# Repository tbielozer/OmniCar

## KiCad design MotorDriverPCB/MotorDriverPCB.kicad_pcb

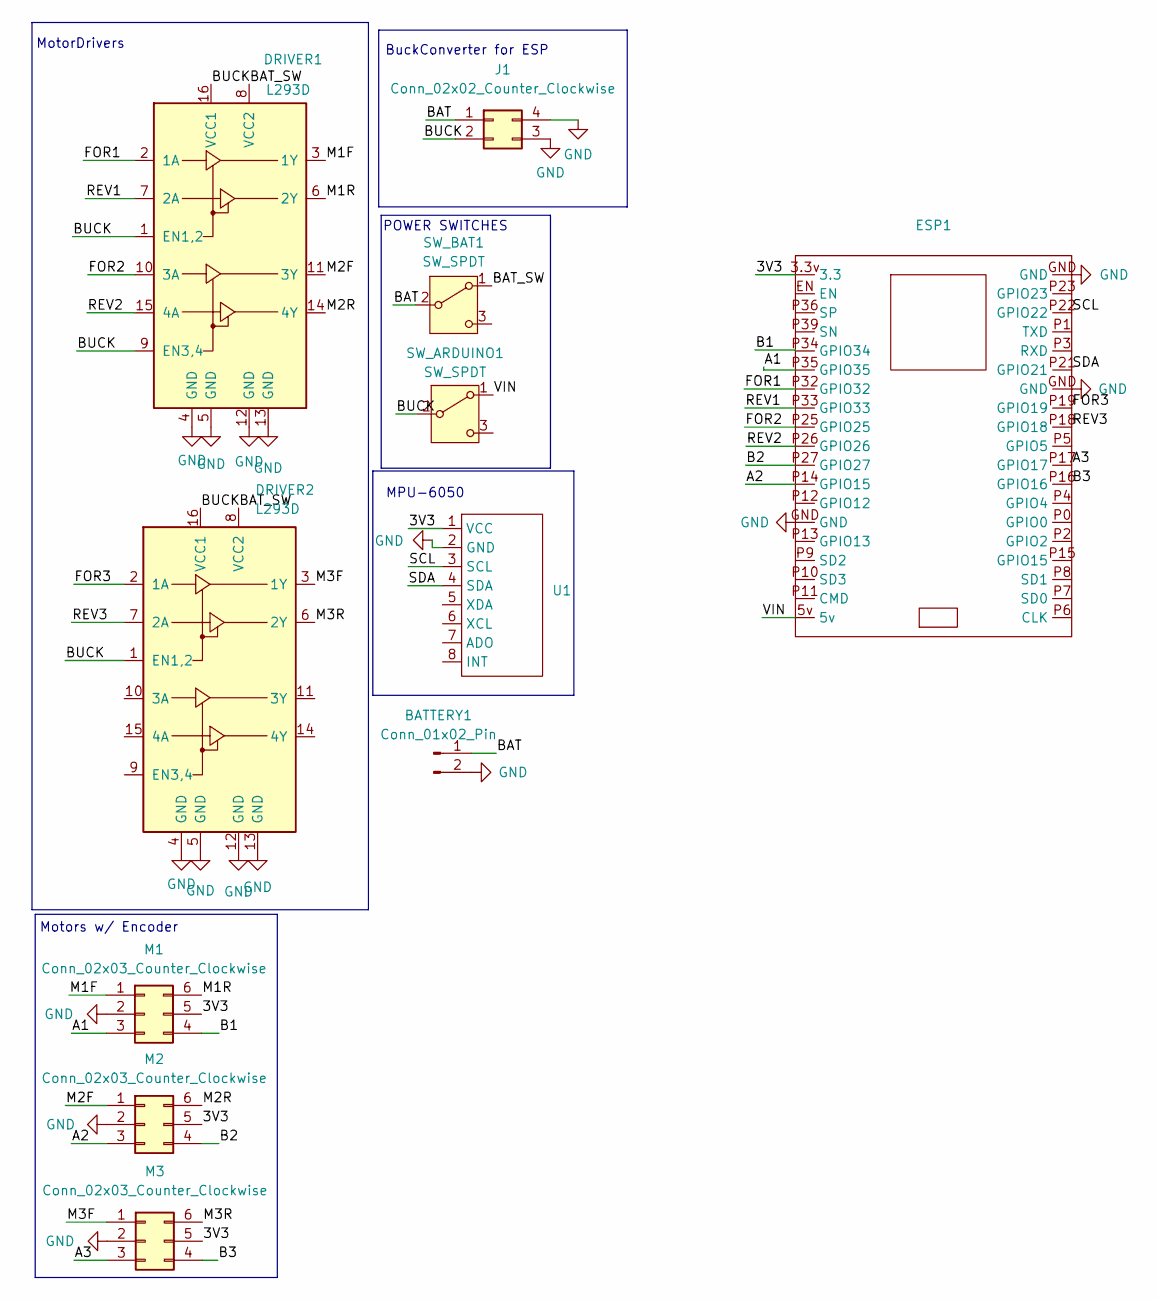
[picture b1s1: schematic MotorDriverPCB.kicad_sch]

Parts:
BATTERY1: Conn_01x02_Pin; PinHeader_1x02_P2.54mm_Vertical
DRIVER1, DRIVER2: L293D; DIP-16_W7.62mm
ESP1: ESP 38pin
J1: Conn_02x02_Counter_Clockwise; PinHeader_2x02_P2.54mm_Vertical
M1, M2, M3: Conn_02x03_Counter_Clockwise; Header_02x03
SW_ARDUINO1: SW_SPDT; SW_SLIDE_SPDT_2.54mm
SW_BAT1: SW_SPDT; SW_SLIDE_SPDT_2.54mm
U1: MPU-6050-Breakout

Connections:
/3V3: ESP1.3.3v (3.3), M1.5, M2.5, M3.5, U1.1 (VCC)
/A1: ESP1.P35 (GPIO35), M1.3
/A2: ESP1.P14 (GPIO15), M2.3
/A3: ESP1.P17 (GPIO17), M3.3
/B1: ESP1.P34 (GPIO34), M1.4
/B2: ESP1.P27 (GPIO27), M2.4
/B3: ESP1.P16 (GPIO16), M3.4
/BAT: BATTERY1.1, J1.1, SW_BAT1.2 (B)
/BAT_SW: DRIVER1.8 (VCC2), DRIVER2.8 (VCC2), SW_BAT1.1 (A)
/BUCK: DRIVER1.1 (EN1,2), DRIVER1.9 (EN3,4), DRIVER1.16 (VCC1), DRIVER2.1 (EN1,2), DRIVER2.16 (VCC1), J1.2, SW_ARDUINO1.2 (B)
/FOR1: DRIVER1.2 (1A), ESP1.P32 (GPIO32)
/FOR2: DRIVER1.10 (3A), ESP1.P25 (GPIO25)
/FOR3: DRIVER2.2 (1A), ESP1.P19 (GPIO19)
/M1F: DRIVER1.3 (1Y), M1.1
/M1R: DRIVER1.6 (2Y), M1.6
/M2F: DRIVER1.11 (3Y), M2.1
/M2R: DRIVER1.14 (4Y), M2.6
/M3F: DRIVER2.3 (1Y), M3.1
/M3R: DRIVER2.6 (2Y), M3.6
/REV1: DRIVER1.7 (2A), ESP1.P33 (GPIO33)
/REV2: DRIVER1.15 (4A), ESP1.P26 (GPIO26)
/REV3: DRIVER2.7 (2A), ESP1.P18 (GPIO18)
/SCL: ESP1.P22 (GPIO22), U1.3 (SCL)
/SDA: ESP1.P21 (GPIO21), U1.4 (SDA)
/VIN: ESP1.5v, SW_ARDUINO1.1 (A)
GND: BATTERY1.2, DRIVER1.4 (GND), DRIVER1.5 (GND), DRIVER1.12 (GND), DRIVER1.13 (GND), DRIVER2.4 (GND), DRIVER2.5 (GND), DRIVER2.12 (GND), DRIVER2.13 (GND), ESP1.GND, J1.3, J1.4, M1.2, M2.2, M3.2, U1.2 (GND)

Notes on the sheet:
POWER SWITCHES
MotorDrivers
BuckConverter for ESP
MPU-6050
Motors w/ Encoder

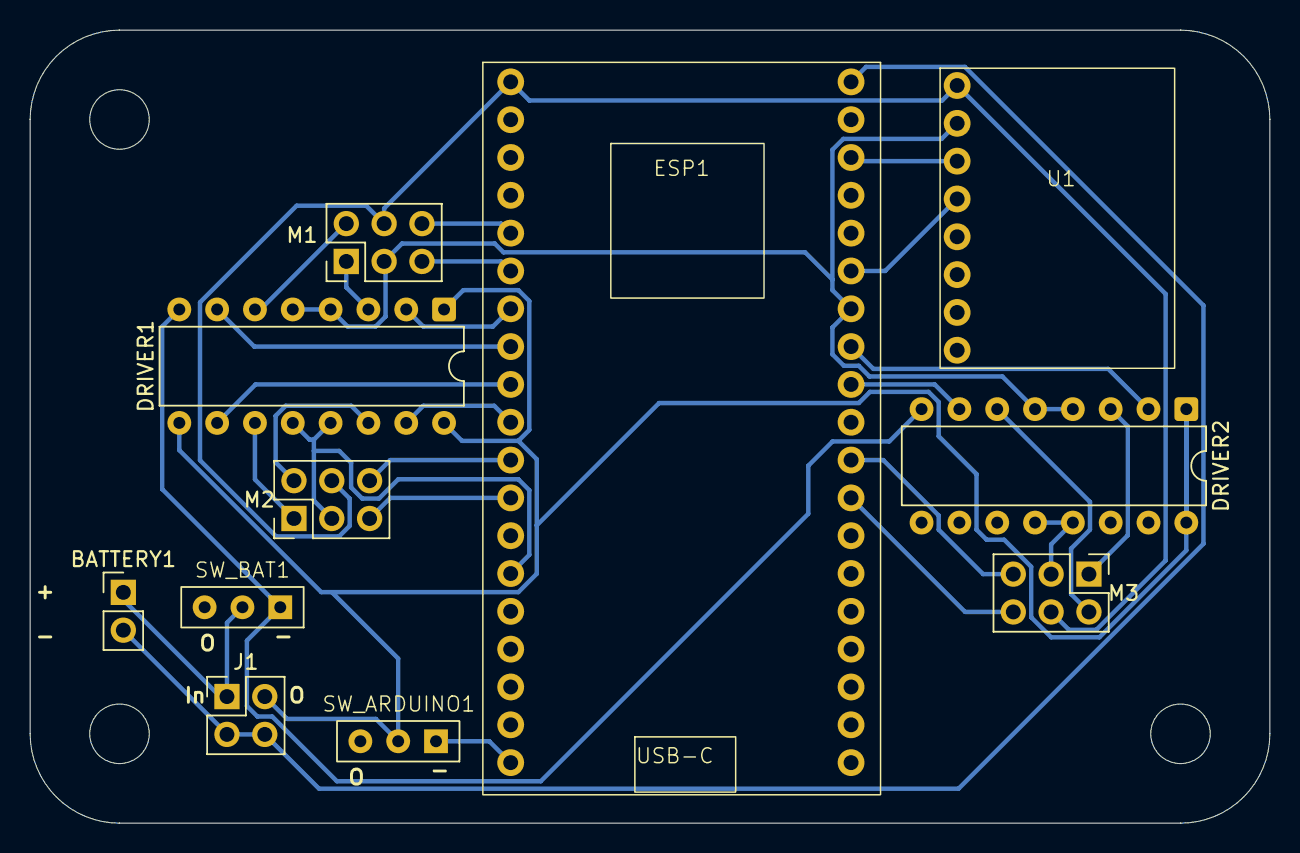
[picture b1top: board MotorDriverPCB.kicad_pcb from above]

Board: 2 copper layers, 83.3 x 53.3 mm, 11 parts (0 on the bottom side), 26 nets.
